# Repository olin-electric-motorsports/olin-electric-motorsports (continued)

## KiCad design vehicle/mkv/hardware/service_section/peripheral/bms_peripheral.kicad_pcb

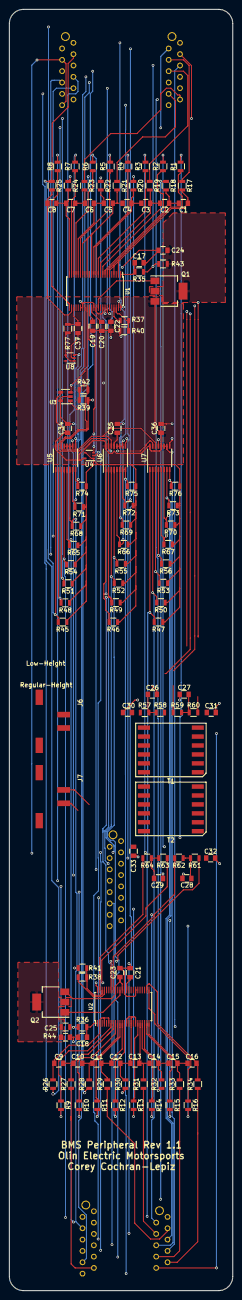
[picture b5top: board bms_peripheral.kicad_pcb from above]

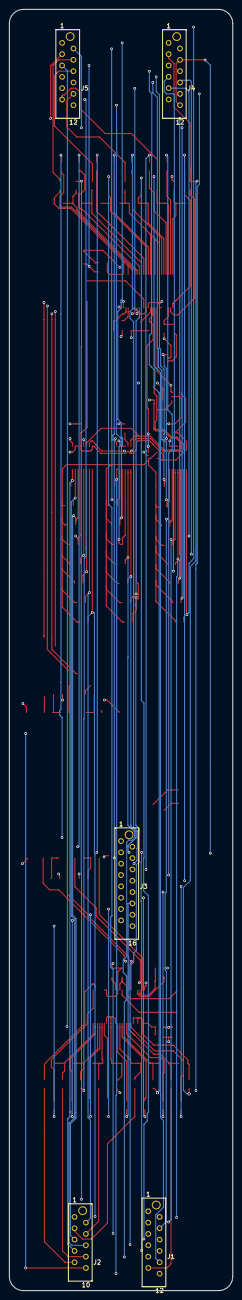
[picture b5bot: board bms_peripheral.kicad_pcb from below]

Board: 4 copper layers, 50.0 x 287.0 mm, 133 parts (5 on the bottom side), 138 nets.

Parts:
C1, C2, C3, C4, C5, C6, C7, C8, C9, C10, C11, C12, C13, C14, C15, C16, C26, C27, C28, C29, C30, C31, C32, C33, C37: C_10nF; C_0805_OEM
C17, C18, C24, C25: C_0.1uF; C_0805_OEM
C19, C20, C21, C22, C23: 1uF; C_0805_OEM
C34, C35, C36: C_1uF; C_0805_OEM
J1, J4: MM_F_VT_12; micromatch_female_vt_12
J2: MM_F_VT_10; micromatch_female_vert_10
J3: MM_F_VT_16; micromatch_female_vert_16
J5: MM_M_VT_12; micromatch_female_vt_12
J6, J7: MicroFit_RA_V_2_SMD; MicroFit_RA_2_SMD
Q1, Q2: NSS1C201MZ4; SOT-223
R1, R2, R3, R4, R5, R6, R7, R8, R9, R10, R11, R12, R13, R14, R15, R16, R39, R42: R_4.99K; R_0805_OEM
R17, R18, R19, R20, R21, R22, R23, R24, R25, R26, R27, R28, R29, R30, R31, R32, R33, R34, R35, R36, R43, R44, R77: R_100; R_0805_OEM
R37, R38, R40, R41: R_1K; R_0805_OEM
R45, R46, R47, R48, R49, R50, R51, R52, R53, R54, R55, R56, R65, R66, R67, R68, R69, R70, R71, R72, R73, R74, R75, R76: R_100K; R_0805_OEM
R57, R58, R59, R60, R61, R62, R63, R64: R_60.4; R_0805_OEM
T1, T2: T_LAN_SM91501ALE
U1, U2: LTC6811-1; TSSOP-48_LTC6811-1
U3: 24AA01; SOT-23-5_OEM_24AA01
U4, U8: MCP6001T-I-LT; SOT-353_SC-70-5
U5, U6, U7: LTC1380IGN; SSOP-16_3.9x4.9mm_P0.635mm

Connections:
/C0: J2.9, R34.1
/C1: J2.8, R33.1
/C1_T1: J2.7, R76.2, U7.8
/C1_T2: J2.6, R73.2, U7.7
/C1_T3: J2.5, R70.2, U7.6
/C2: J4.11, R32.1
/C3: J2.4, R31.1
/C3_T1: J4.9, R67.2, U7.5
/C3_T2: J4.8, R56.2, U7.4
/C3_T3: J4.7, R53.2, U7.3
/C4: J4.10, R30.1
/C5: J2.3, R29.1
/C5_T1: J2.2, R50.2, U7.2
/C5_T2: J2.1, R47.2, U7.1
/C5_T3: J1.12, R75.2, U6.8
/C6: J4.6, R28.1
/C7: J1.11, R27.1
/C7_T1: J4.2, R72.2, U6.7
/C7_T2: J4.1, R69.2, U6.6
/C7_T3: J5.12, R66.2, U6.5
/C8: J4.3, R25.1, R26.1
/C9: J1.10, R24.1
/C9_T1: J1.9, R55.2, U6.4
/C9_T2: J1.8, R52.2, U6.3
/C9_T3: J1.7, R49.2, U6.2
/C10: J5.11, R23.1
/C11: J1.6, R22.1
/C11_T1: J5.9, R46.2, U6.1
/C11_T2: J5.8, R74.2, U5.8
/C11_T3: J5.7, R71.2, U5.7
/C12: J5.10, R21.1
/C13: J1.5, R20.1
/C13_T1: J1.4, R68.2, U5.6
/C13_T2: J1.3, R65.2, U5.5
/C13_T3: J1.2, R54.2, U5.4
/C14: J5.6, R19.1
/C15: J1.1, R18.1
/C15_T1: J5.3, R51.2, U5.3
/C15_T2: J5.2, R48.2, U5.2
/C15_T3: J5.1, R45.2, U5.1
/C16: J5.4, R17.1
/GND1: C18.2, C21.2, C23.2, C25.2, C28.2, C29.2, C32.2, C33.2, J4.4, J4.12, R41.2, U2.30, U2.31, U2.36
/GND2: C17.2, C19.2, C20.2, C22.2, C24.2, C26.2, C27.2, C30.2, C31.2, C34.2, C35.2, C36.2, C37.2, J2.10, R40.2, U1.30, U1.31, U1.36, U3.2, U3.5, U4.2, U5.10, U5.11, U5.12, U5.13, U6.10, U6.11, U6.12, U7.10, U7.11, U7.13, U8.2
/IMA1: R62.2, T2.3, U2.41
/IMA2: R58.2, T1.3, U1.41
/IMB1: R64.2, T2.6, U2.47
/IMB2: R60.2, T1.6, U1.47
/IPA1: R61.1, T2.1, U2.42
/IPA2: R57.1, T1.1, U1.42
/IPB1: R63.1, T2.4, U2.48
/IPB2: R59.1, T1.4, U1.48
/Q1: J3.16, R16.2
/Q2: J3.15, R15.2
/Q3: J3.14, R14.2
/Q4: J3.13, R13.2
/Q5: J3.12, R12.2
/Q6: J3.11, R11.2
/Q7: J3.10, R10.2
/Q8: J3.9, R9.2
/Q9: J3.8, R8.2
/Q10: J3.7, R7.2
/Q11: J3.6, R6.2
/Q12: J3.5, R5.2
/Q13: J3.4, R4.2
/Q14: J3.3, R3.2
/Q15: J3.2, R2.2
/Q16: J3.1, R1.2
/SCL: R42.2, U1.33, U3.1, U5.15, U6.15, U7.15
/SDA: R39.2, U1.32, U3.3, U5.14, U6.14, U7.14
/TEMP_SENSE: C37.1, R77.1, U1.27
/V+1: J5.5, R36.1, R44.1
/V+2: J4.5, R35.1, R43.1
/VREF2: R45.1, R46.1, R47.1, R48.1, R49.1, R50.1, R51.1, R52.1, R53.1, R54.1, R55.1, R56.1, R65.1, R66.1, R67.1, R68.1, R69.1, R70.1, R71.1, R72.1, R73.1, R74.1, R75.1, R76.1, U4.1, U4.4
/VREG: C22.1, C34.1, C35.1, C36.1, Q1.3, R39.1, R42.1, U1.37, U1.40, U3.4, U4.5, U5.16, U6.13, U6.16, U7.12, U7.16, U8.5
/~DIS1: R16.1, U2.25
/~DIS2: R15.1, U2.23
/~DIS3: R14.1, U2.21
/~DIS4: R13.1, U2.19
/~DIS6: R12.1, U2.13
/~DIS7: R11.1, U2.11
/~DIS8: R10.1, U2.9
/~DIS9: R9.1, U2.7
unnamed: C1.1, R17.2, U1.2, U1.4, U1.6
unnamed: C1.2, C2.1, R18.2, U1.8
unnamed: C2.2, C3.1, R19.2, U1.10
unnamed: C3.2, C4.1, R20.2, U1.12
unnamed: C4.2, C5.1, R21.2, U1.14, U1.16, U1.18
unnamed: C5.2, C6.1, R22.2, U1.20
unnamed: C6.2, C7.1, R23.2, U1.22
unnamed: C7.2, C8.1, R24.2, U1.24
unnamed: C8.2, R25.2, U1.26
unnamed: C9.1, R26.2, U2.2, U2.4, U2.6
unnamed: C9.2, C10.1, R27.2, U2.8
unnamed: C10.2, C11.1, R28.2, U2.10
unnamed: C11.2, C12.1, R29.2, U2.12
unnamed: C12.2, C13.1, R30.2, U2.14, U2.16, U2.18
unnamed: C13.2, C14.1, R31.2, U2.20
unnamed: C14.2, C15.1, R32.2, U2.22
unnamed: C15.2, C16.1, R33.2, U2.24
unnamed: C16.2, R34.2, U2.26
unnamed: C17.1, R35.2, U1.1
unnamed: C18.1, R36.2, U2.1
unnamed: C19.1, U1.34, U4.3
unnamed: C20.1, U1.35
unnamed: C21.1, U2.35
unnamed: C23.1, Q2.3, U2.37, U2.40
unnamed: C24.1, Q1.2, Q1.4, R43.2
unnamed: C25.1, Q2.2, Q2.4, R44.2
unnamed: C26.1, R57.2, R58.1
unnamed: C27.1, R59.2, R60.1
unnamed: C28.1, R61.2, R62.1
unnamed: C29.1, R63.2, R64.1
unnamed: C30.1, T1.2
unnamed: C31.1, T1.5
unnamed: C32.1, T2.2
unnamed: C33.1, T2.5
unnamed: J6.1, T1.12
unnamed: J6.2, T1.10
unnamed: J7.1, T2.9
unnamed: J7.2, T2.7
unnamed: Q1.1, U1.38
unnamed: Q2.1, U2.38
unnamed: R1.1, U1.7
unnamed: R2.1, U1.9
unnamed: R3.1, U1.11
unnamed: R4.1, U1.13
unnamed: R5.1, U1.19
unnamed: R6.1, U1.21
unnamed: R7.1, U1.23
unnamed: R8.1, U1.25
unnamed: R37.1, R40.1, U1.46
unnamed: R37.2, U1.45
unnamed: R38.1, R41.1, U2.46
unnamed: R38.2, U2.45
unnamed: R77.2, U8.1, U8.4
unnamed: T1.7, T2.10
unnamed: T1.9, T2.12
unnamed: U5.9, U6.9, U7.9, U8.3

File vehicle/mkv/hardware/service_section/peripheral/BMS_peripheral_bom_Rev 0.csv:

Component,Description,Part,References,Value,Footprint,Quantity Per PCB,Datasheet,MPN,MFN,PurchasingLink
1,"Capacitor, 1uF, 25V, 10%, 0805",C_1uF,C19 C20 C21 C22 C23,1uF,C_0805_OEM,5,http://www.samsungsem.com/kr/support/product-search/mlcc/__i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,1276-2887-1-ND,DK,https://www.digikey.com/product-detail/en/samsung-electro-me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
2,"Capacitor, 0.1uF, 50V, 5%, 0805",C_0.1uF,C17 C18 C24 C25,C_0.1uF,C_0805_OEM,4,http://datasheets.avx.com/X7RDielectric.pdf,478-3352-1-ND,DK,https://www.digikey.com/products/en?keywords=478-3352-1-ND
3,"Capacitor, 10nF 50V X7R 0805",C_10nF,C1 C2 C3 C4 C5 C6 C7 C8 C9 C10 C11 C12 C13 C14 C15 C16 C26 C27 C28 C29 C30 C31 C32 C33 C37,C_10nF,C_0805_OEM,25,http://www.samsungsem.com/kr/support/product-search/mlcc/__i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,1276-1015-1-ND,DK,https://www.digikey.com/product-detail/en/samsung-electro-me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
4,"Capacitor, 1uF, 25V, 10%, 0805",C_1uF,C34 C35 C36,C_1uF,C_0805_OEM,3,http://www.samsungsem.com/kr/support/product-search/mlcc/__i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,1276-2887-1-ND,DK,https://www.digikey.com/product-detail/en/samsung-electro-me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
5,Micro-MaTch connector 10 pin female vertical,MM_F_VT_10,J2,MM_F_VT_10,micromatch_female_vert_10,1,http://www.te.com/commerce/DocumentDelivery/DDEController?Ac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,1-338068-0,TE,http://www.te.com/global-en/product-1-338068-0.html
6,Micro-MaTch connector 12 pin female vertical,MM_F_VT_12,J1 J4,MM_F_VT_12,micromatch_female_vt_12,2,http://www.te.com/commerce/DocumentDelivery/DDEController?Ac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,1-338068-2,TE,http://www.te.com/global-en/product-1-338068-2.html
7,Micro-MaTch connector 16 pin female vertical,MM_F_VT_16,J3,MM_F_VT_16,micromatch_female_vert_16,1,http://www.te.com/commerce/DocumentDelivery/DDEController?Ac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,1-338068-6,TE,http://www.te.com/global-en/product-1-338068-6.html
8,Micro-MaTch connector 12 pin male vertical,MM_M_VT_12,J5,MM_M_VT_12,micromatch_female_vt_12,1,http://www.te.com/commerce/DocumentDelivery/DDEController?Ac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,1-215464-2,TE,http://www.te.com/global-en/product-1-215464-2.html
9,"100V, 2.0A, Low VCE NPN Transistor",NSS1C201MZ4,Q1 Q2,NSS1C201MZ4,SOT-223,2,http://www.onsemi.com/pub/Collateral/NSS1C201MZ4-D.PDF,NSS1C201MZ4T3GOSCT-ND,DK,https://www.digikey.com/product-detail/en/on-semiconductor/N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
10,"Resistor, 100, 0.25W, 1%, 0805",R_100,R17 R18 R19 R20 R21 R22 R23 R24 R25 R26 R27 R28 R29 R30 R31 R32 R33 R34 R35 R36 R43 R44 R77,R_100,R_0805_OEM,23,https://www.seielect.com/Catalog/SEI-rncp.pdf,RNCP0805FTD100RCT-ND,DK,https://www.digikey.com/products/en?keywords=RNCP0805FTD100RCT-ND
11,"Resistor, 100K, 0.125W, 1%, 0805",R_100K,R45 R46 R47 R48 R49 R50 R51 R52 R53 R54 R55 R56 R65 R66 R67 R68 R69 R70 R71 R72 R73 R74 R75 R76,R_100K,R_0805_OEM,24,https://industrial.panasonic.com/cdbs/www-data/pdf/RDA0000/A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,P100KCCT-ND,DK,https://www.digikey.com/product-detail/en/panasonic-electron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
12,"Resistor, 1K, 0.25W, 1%, 0805",R_1K,R37 R38 R40 R41,R_1K,R_0805_OEM,4,https://www.seielect.com/Catalog/SEI-rncp.pdf,RNCP0805FTD1K00CT-ND,DK,https://www.digikey.com/products/en?keywords=RNCP0805FTD1K00CT-ND
13,4.99k resistor,R_4.99K,R1 R2 R3 R4 R5 R6 R7 R8 R9 R10 R11 R12 R13 R14 R15 R16 R39 R42,R_4.99K,R_0805_OEM,18,https://www.digikey.com/product-detail/en/yageo/RC0402FR-074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,RNCP0805FTD4K99CT-ND,DK,https://www.digikey.com/product-detail/en/stackpole-electron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
14,"Resistor, 60.4, 0.1%, 0.125W, 0805",R_60.4,R57 R58 R59 R60 R61 R62 R63 R64,R_60.4,R_0805_OEM,8,https://industrial.panasonic.com/cdbs/www-data/pdf/RDM0000/A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,P60.4DACT-ND,DK,https://www.digikey.com/product-detail/en/panasonic-electron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
15,Transformer LAN 10/100 base-T,T_LAN_7490100111A,T1 T2,T_LAN_7490100111A,T_LAN_7490100111A,2,https://katalog.we-online.de/pbs/datasheet/7490100111A.pdf,732-5711-1-ND,DK,https://www.digikey.com/product-detail/en/wurth-electronics-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
16,IC EEPROM 1K I2C 400KHZ 8DIP,24AA01,U3,24AA01,SOT-23-5_OEM_24AA01,1,http://ww1.microchip.com/downloads/en/DeviceDoc/21711J.pdf,CAT24AA01TDI-GT3OSCT-ND,DK,https://www.digikey.com/product-detail/en/on-semiconductor/C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
17,Single-Ended 8-Channel/ Differential 4-Channel Analog Multiplexer with SMBus Interface,LTC1380IGN,U5 U6 U7,LTC1380IGN,SSOP-16_3.9x4.9mm_P0.635mm,3,https://www.analog.com/media/en/technical-documentation/data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,LTC1380IGN#PBF-ND,DK,https://www.digikey.com/product-detail/en/linear-technology-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
18,LTC6811-1,LTC6811-1,U1 U2,LTC6811-1,TSSOP-48_LTC6811-1,2,https://www.analog.com/media/en/technical-documentation/data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,LTC6811IG-1-PBF-ND,DK,https://www.digikey.com/product-detail/en/linear-technology-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
19,"Single op-amp, general purpose, -40-+85 C, SC-70-5",MCP6001T-I-LT,U4 U8,MCP6001T-I-LT,SOT-353_SC-70-5,2,http://ww1.microchip.com/downloads/en/DeviceDoc/21733j.pdf,MCP6001T-I/LTCT-ND,DK,https://www.digikey.com/product-detail/en/microchip-technolo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
,,,,,,,,,,
,,,,,,,,,,
,,,,,,,,,,
,,,,,,,,,,
,,,,,,,,,,
Component Groups:,19,,,,,,,,,
Component Count:,131,,,,,,,,,
Fitted Components:,131,,,,,,,,,
Number of PCBs:,1,,,,,,,,,
Total components:,131,,,,,,,,,
Schematic Version:,Rev 0,,,,,,,,,
Schematic Date:,2019-09-17,,,,,,,,,
PCB Variant:,default,,,,,,,,,
BoM Date:,Mon 11 Nov 2019 08:39:12 PM EST,,,,,,,,,
Schematic Source:,/home/vscheyer/Desktop/Formula/MKV-Boards/Boards/BMS_Peripheral/BMS_peripheral.sch,,,,,,,,,
KiCad Version:,Eeschema 5.0.2-bee76a0~70~ubuntu16.04.1,,,,,,,,,

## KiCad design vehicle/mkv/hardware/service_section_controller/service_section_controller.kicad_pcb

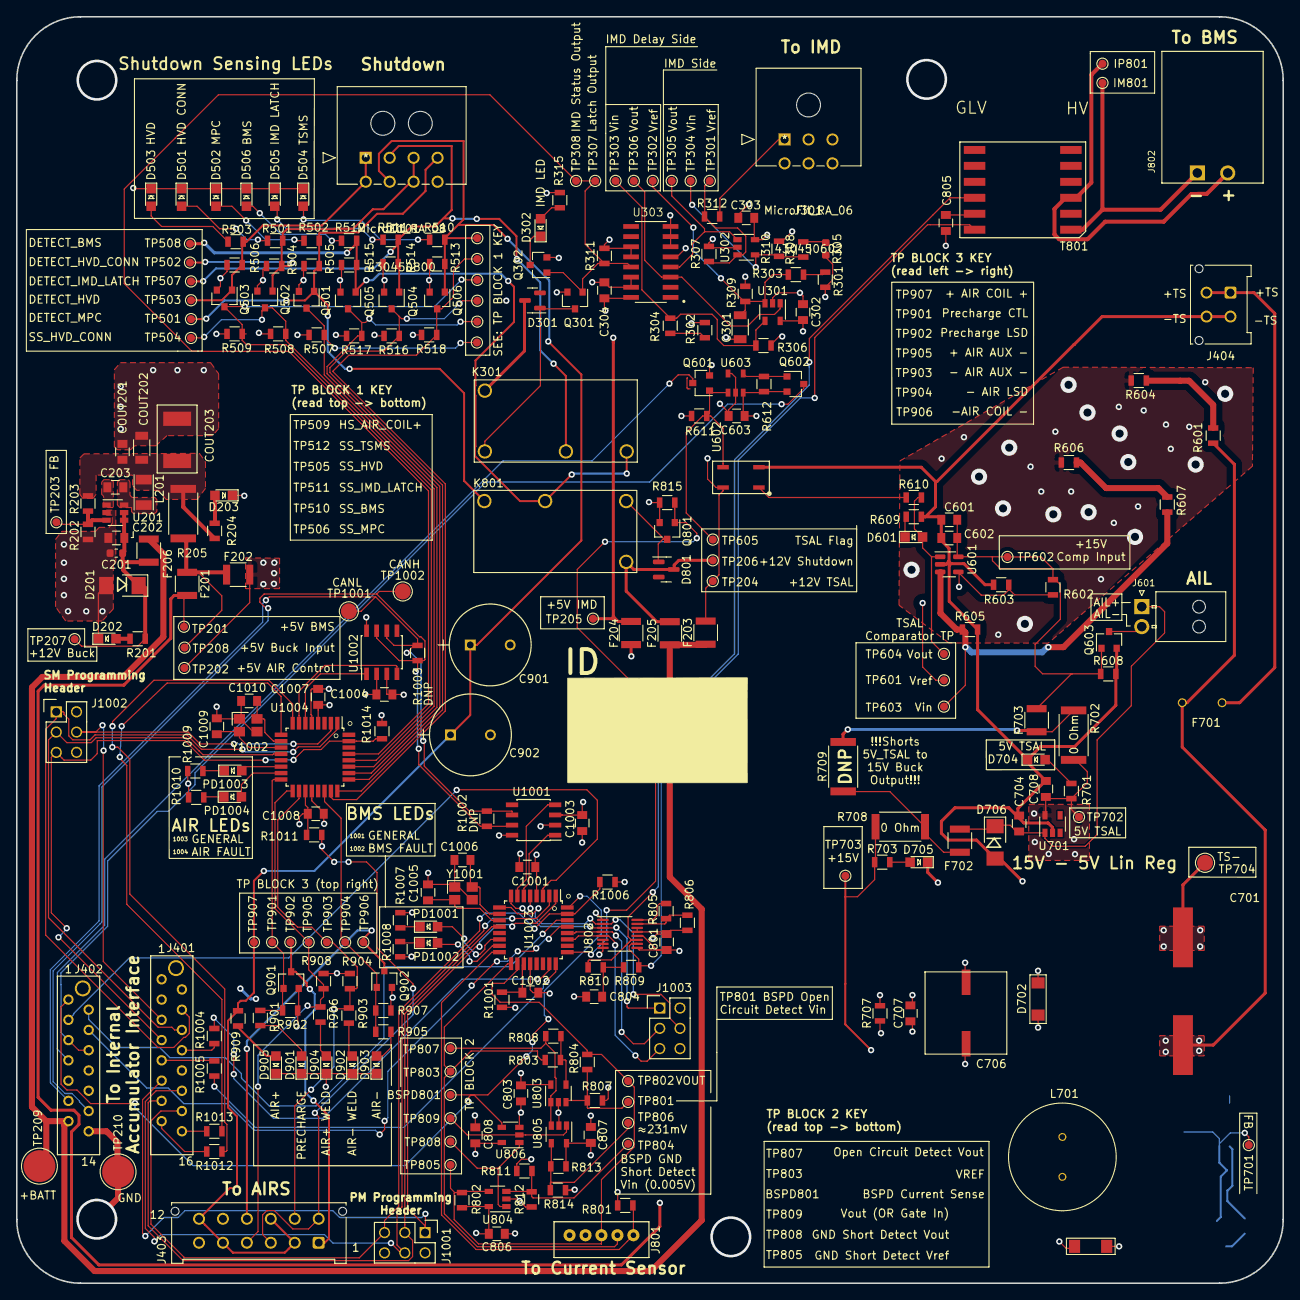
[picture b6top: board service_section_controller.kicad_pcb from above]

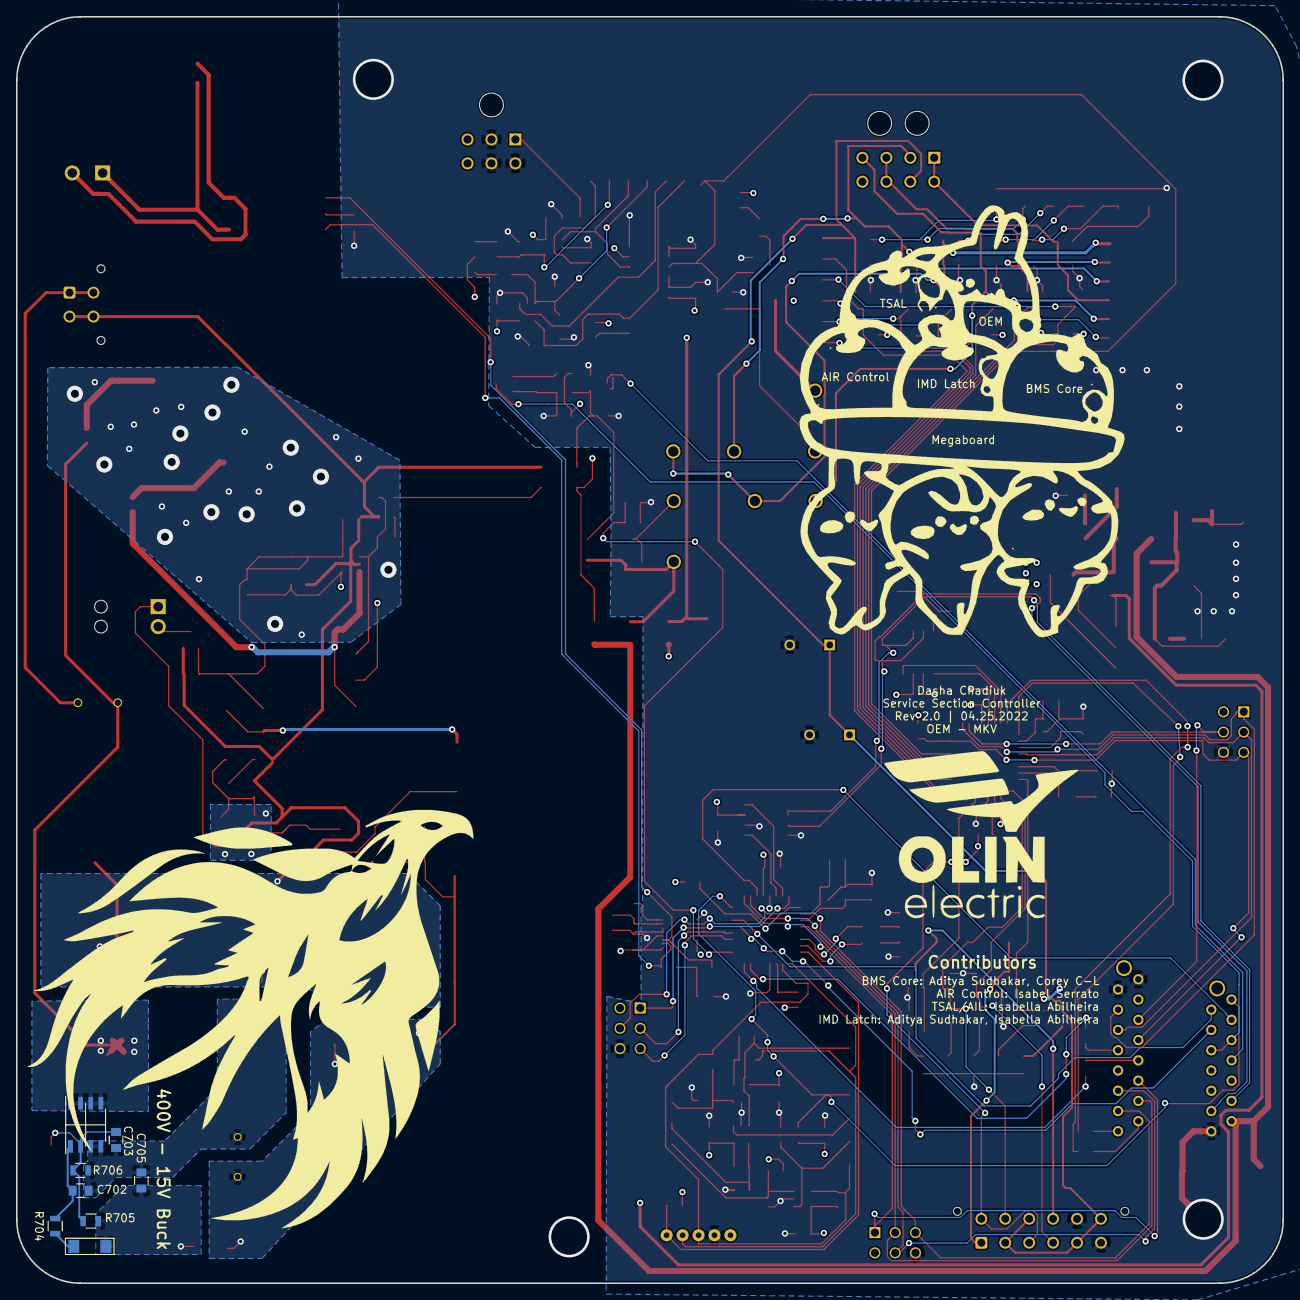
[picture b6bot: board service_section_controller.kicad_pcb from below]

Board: 4 copper layers, 158.8 x 158.8 mm, 283 parts (8 on the bottom side), 151 nets.

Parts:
BSPD801: Test_Point_SMD; TestPoint_Pad_D1.0mm
C201: C_2.2uF; C_0603_1608Metric
C202, C203, C302, C303, C304, C602, C801, C803, C806, C807, C808, C1001, C1003, C1004, C1007: C_0.1uF; C_0805_OEM
C301: C_22uF; C_1206_OEM
C601: C_10uF; C_0805_OEM
C603, C704, C707, C708: C_1uF; C_0805_OEM
C701: C_10uF_450V
C702: C_2.2uF; C_0805_OEM
C703: C_470pF; C_0805_OEM
C705: C_.22uF; C_0805_OEM
C706: C_100uF+
C804, C805: C_10nF; C_0805_OEM
C901, C902: CP_1mF; C_Radial_D10_L13_P5_OEM
C1002, C1008: C_100pF; C_0805_OEM
C1005, C1006, C1009, C1010: C_30pF; C_0805_OEM
COUT201: C_47uF; C_0805_OEM
COUT202: C_22uF; C_1206_OEM
COUT203: C_33uF; Fuse_1812
D201, D706: D_Zener_18V; DO-214AA
D202, D203, D302, D501, D502, D503, D504, D505, D506, D601, D704, D705, D901, D902, D903, D904, D905: LED_0805; LED_0805_OEM
D301, D801: BAS40-00; SOT-23
D701, D702, D703: Diode_600V_1A_SM
F201, F202, F203, F204, F205, F206, F702, F703: 500mA; Fuse_1210
F701: F_21mA_420V
IM801: Test_Point_SMD; TestPoint_Pad_D1.0mm
IP801: Test_Point_SMD; TestPoint_Pad_D1.0mm
J301: MicroFit_RA_06; 430450602
J401: MM_F_VT_16; micromatch_female_vert_16
J402: MM_F_VT_14; micromatch_female_vert_14
J403: MicroFit_VT_12
J404: MicroFit_VT_4
J601: NanoFit_2; NanoFit_Molex_1x02x2.50mm_Angled_OEM
J801: B5B-PH-K-S
J802: isoSPI-Cutout; iso_spi_cutout
J1001, J1002, J1003: CONN_02X03; Pin_Header_Straight_2x03
J1101: MicroFit_RA_08; 430450800
K301, K801: G5Q-1A4-DC12; Relay_SPST_OMRON-G5Q-1A4_OEM
L201: L_100uH; L_100uH_OEM
L701: L_1.2mH
PD1001, PD1002, PD1003, PD1004: LED_0805; LED_0805_OEM
Q301, Q302, Q501, Q502, Q503, Q504, Q505, Q506, Q601, Q602, Q603, Q801, Q901, Q902: SSM3K333R; SOT-23F
R201, R301, R307, R315, R501, R502, R503, R510, R511, R512, R602, R609, R703, R805, R806, R812, R909: R_1K; R_0805_OEM
R202: R_25K; R_0805_OEM
R203, R310, R504, R505, R506, R513, R514, R515: R_100K; R_0805_OEM
R204, R701, R901, R903, R905, R906, R1004, R1005, R1007, R1008, R1009, R1010, R1012, R1013: R_200; R_0805_OEM
R205, R702, R708, R709: R_0_2512; R_2512_OEM
R302: R_2.2K; R_0805_OEM
R303: R_120K; R_0805_OEM
R304: R_300K; R_0805_OEM
R305: R_0; R_0603_1608Metric
R306, R311: R_604K; R_0805_OEM
R308: R_200K; R_0805_OEM
R309: R_1.82M; R_0805_OEM
R312, R707: R_3K; R_0805_OEM
R507, R508, R509, R516, R517, R518, R605, R608, R611, R612, R704, R801, R802, R803, R804, R807, R808, R814, R815, R902, R904, R907, R908, R1006, R1014: R_10K; R_0805_OEM
R601, R604, R606, R607: R_270K; R_0805_OEM
R603: R_120; R_0805_OEM
R610: R_499; R_0805_OEM
R705: R_23.7K; R_0805_OEM
R706: R_4.99K; R_0805_OEM
R809, R810: R_60.4; R_0805_OEM
R811: R_1M; R_0805_OEM
R813: R_475; R_0805_OEM
R1001, R1011: R_100; R_0805_OEM
R1002, R1003: R_120_DNP; R_0805_OEM
T801: T_LAN_SM91501ALE
TP201: 5V_BMS; TestPoint_Pad_D1.0mm
TP202: 5V_AIR_CONTROL; TestPoint_Pad_D1.0mm
TP203, TP701: FB; TestPoint_Pad_D1.0mm
TP204: 12V_TSAL; TestPoint_Pad_D1.0mm
TP205: 5V_IMD; TestPoint_Pad_D1.0mm
TP206: 12V_SHUTDOWN; TestPoint_Pad_D1.0mm
TP207: 12V_BUCK; TestPoint_Pad_D1.0mm
TP208: BUCK_OUTPUT; TestPoint_Pad_D1.0mm
TP209: +Batt; TestPoint_Pad_D4.0mm
TP210: LV_GND; TestPoint_Pad_D4.0mm
TP301: IMD_OUTPUT; TestPoint_Pad_D1.0mm
TP302, TP303, TP306, TP801, TP804, TP805, TP806, TP807, TP808, TP809: Test_Point_SMD; TestPoint_Pad_D1.0mm
TP304: 1.6V_OPAMP; TestPoint_Pad_D1.0mm
TP305: OPAMP_OUTPUT; TestPoint_Pad_D1.0mm
TP307: LATCH_OUTPUT; TestPoint_Pad_D1.0mm
TP308: IMD_STATUS_OUTPUT; TestPoint_Pad_D1.0mm
TP501: DETECT_MPC; TestPoint_Pad_D1.0mm
TP502: DETECT_HVD_CONN; TestPoint_Pad_D1.0mm
TP503: DETECT_HVD; TestPoint_Pad_D1.0mm
TP504: SS_HVD_CONN; TestPoint_Pad_D1.0mm
TP505: SS_HVD; TestPoint_Pad_D1.0mm
TP506: SS_MPC; TestPoint_Pad_D1.0mm
TP507: DETECT_IMD_LATCH; TestPoint_Pad_D1.0mm
TP508: DETECT_BMS; TestPoint_Pad_D1.0mm
TP509: DETECT_TSMS; TestPoint_Pad_D1.0mm
TP510: SS_BMS; TestPoint_Pad_D1.0mm
TP511: SS_IMD_LATCH; TestPoint_Pad_D1.0mm
TP512: SS_TSMS; TestPoint_Pad_D1.0mm
TP601, TP803: VREF; TestPoint_Pad_D1.0mm
TP602: 5V+; TestPoint_Pad_D1.0mm
TP603: VIN; TestPoint_Pad_D1.0mm
TP604: COMPARATOR_OUTPUT; TestPoint_Pad_D1.0mm
TP605: TSAL_FLAG; TestPoint_Pad_D1.0mm
TP702: 5V_TSAL; TestPoint_Pad_D1.0mm
TP703: 15V+_OUTPUT; TestPoint_Pad_D1.0mm
TP704: TS-; TestPoint_Pad_D2.0mm
TP802: VOUT; TestPoint_Pad_D1.0mm
TP901: PRECHARGE_CTL; TestPoint_Pad_D1.0mm
TP902: PRECHARGE_LSD; TestPoint_Pad_D1.0mm
TP903: -AIR_WELD_DETECT; TestPoint_Pad_D1.0mm
TP904: -AIR_LSD; TestPoint_Pad_D1.0mm
TP905: +AIR_WELD_DETECT; TestPoint_Pad_D1.0mm
TP906: -AIR_COIL-; TestPoint_Pad_D1.0mm
TP907: +AIR_COIL+; TestPoint_Pad_D1.0mm
TP1001: CAN_L; TestPoint_Pad_D2.0mm
TP1002: CANH; TestPoint_Pad_D2.0mm
U201: TPS560430YF; SOT-23-6_OEM
U301, U302: TLV3701QDBVRG4Q1; SOT-23-5_OEM
U303: CD4044BDR; SOIC127P600X175-16N
U601: MCP6001; SOT-23-5
U602: CPC1025NTR; 4-pin_SOP
U603: BU4S11G2-TR; SSOP5
U701: AP7370; SOT-23-5
U702: MP9488; Converter_DCDC_MPS_MP9488
U802: LTC6820HMS; MSOP-16_3x4mm_P0.5mm
U803, U804, U805: MCP6001; SOT-23-5_OEM
U806: SN74LVC1G32DBVR; SOT-23-5_OEM
U1001, U1002: MCP2561-E_SN; SOIC-8_3.9x4.9mm_Pitch1.27mm_OEM
U1003: ATMEGA64M1; TQFP-32_7x7mm_Pitch0.8mm
U1004: ATMEGA16M1; TQFP-32_7x7mm_Pitch0.8mm
Y1001, Y1002: Crystal_SMD; Crystal_SMD_FA238

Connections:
+5V: F201.1, F202.1, R205.1, TP208.1
+5V_AIR_CONTROL: C1004.1, C1007.1, F202.2, F204.1, J401.10, J403.3, J403.7, J1002.2, R507.1, R508.1, R509.1, R516.1, R517.1, R518.1, R1011.1, R1014.1, TP202.1, U1002.3, U1004.4
+5V_BMS: C801.1, C803.1, C806.1, C807.1, C808.1, C1001.1, C1003.1, F201.2, J401.3, J801.1, J1001.2, J1003.2, R801.1, R802.2, R811.1, R813.2, R1001.1, R1006.1, TP201.1, U802.6, U802.7, U802.8, U802.9, U802.12, U803.5, U804.5, U805.5, U806.5, U1001.3, U1003.4
+5V_IMD: C302.2, C303.2, C304.2, F204.2, R301.2, R302.2, R305.2, R315.1, TP205.1, U301.5, U302.5, U303.5, U303.16
+5V_TSAL: F703.1, R702.2, R709.2
+5V__TSAL_FUSED: C601.2, C602.2, F703.2, Q603.1, R602.2, R608.1, TP602.1, U601.5
+12V_SHUTDOWN: D301.3, D801.3, F205.2, J301.3, K301.5, K801.5, TP206.1
+12V_TSAL: C603.2, F203.2, J402.8, J402.9, J402.10, TP204.1, U602.4, U603.2, U603.5
+15V: F702.1, R708.1, R709.1
+15V_FUSED: C704.1, D706.1, F702.2, J601.1, U701.1
+AIR_AUX-: J403.4, R906.1, R908.1, TP905.1, U1004.17
+AIR_COIL+: C901.1, C902.1, J403.2, J403.5, J403.9, J403.12, J1101.6, Q506.1, R510.1, R513.1, R909.1, TP509.1, TP907.1
+AIR_COIL-: C201.2, C202.2, C301.2, C302.1, C303.1, C304.1, C603.1, C801.2, C803.2, C804.2, C805.2, C806.2, C807.2, C808.2, C901.2, C902.2, C1001.2, C1002.2, C1003.2, C1004.2, C1005.2, C1006.2, C1007.2, C1008.2, C1009.2, C1010.2, COUT201.2, COUT202.2, COUT203.2, D201.2, D202.1, D203.1, D501.1, D502.1, D503.1, D504.1, D505.1, D506.1, D901.1, D902.1, D903.1, D904.1, D905.1, J301.2, J301.4, J301.5, J401.1, J401.2, J402.14, J403.6, J403.11, J801.2, J1001.6, J1002.6, J1003.6, Q301.2, Q302.2, Q501.2, Q502.2, Q503.2, Q504.2, Q505.2, Q506.2, Q601.2, Q602.2, Q801.2, Q901.2, Q902.2, R202.2, R306.1, R307.2, R309.2, R310.2, R311.2, R504.2, R505.2, R506.2, R513.2, R514.2, R515.2, R611.2, R612.2, R806.2, R807.1, R812.2, R814.1, R815.1, R902.2, R904.2, R907.2, R908.2, R1007.2, R1008.2, R1009.2, R1010.2, TP210.1, U201.2, U301.2, U302.2, U303.6, U303.7, U303.8, U303.11, U303.12, U303.14, U303.15, U603.3, U802.1, U802.13, U802.14, U803.2, U804.2, U805.2, U806.3, U1001.2, U1001.8, U1002.2, U1002.8, U1003.5, U1003.20, U1004.5, U1004.20, Y1001.2, Y1001.4, Y1002.2, Y1002.4
+BATT: F203.1, F205.1, F206.1, J402.13, TP209.1
+TS: F701.2, J404.1, J404.3
-AIR_AUX-: J403.8, R903.1, R904.1, TP903.1, U1004.18
-AIR_COIL-: J403.10, Q902.3, TP906.1
-AIR_LSD: Q902.1, R905.1, R907.1, TP904.1, U1004.22
-TS: C601.1, C602.1, C701.1, C704.2, C706.2, C707.2, C708.2, D702.1, D704.1, D705.1, D706.2, J404.2, J404.4, Q603.2, R603.2, R605.2, R608.2, R609.2, R707.2, TP704.1, U601.2, U602.2, U701.2
/micros/PM_DBG_1: PD1001.2, U1003.14
/micros/PM_DBG_2: PD1002.2, U1003.15
/micros/PM_RXCAN: U1001.4, U1003.7
/micros/PM_TXCAN: U1001.1, U1003.6
/micros/SM_DBG_1: PD1003.2, U1004.14
/micros/SM_DBG_2: PD1004.2, U1004.15
/micros/SM_RXCAN: U1002.4, U1004.7
/micros/SM_TXCAN: U1002.1, U1004.6
/power_main/+12V_BUCK: C201.1, C202.1, D201.1, F206.2, R201.1, TP207.1, U201.4, U201.5
/power_secondary.sch/FB: C703.1, R705.2, R706.1, TP701.1, U702.2
/power_secondary.sch/SW: C702.2, C703.2, C705.2, D702.2, L701.1, R706.2, U702.3, U702.4
/power_secondary.sch/VCC: C702.1, R704.2, U702.1
/tsal_ail/TSAL_FLAG: Q601.1, R611.1, TP605.1, U602.3, U603.1
AIL-: J601.2, Q603.3
BMS_RELAY_DRIVE: Q801.1, R815.2, U1003.25
BSPD_CURRENT_SENSE: BSPD801.1, J402.1, U806.4, U1003.32
CANH: J402.12, R1002.1, R1003.1, TP1002.1, U1001.7, U1002.7
CANL: J402.11, R1002.2, R1003.2, TP1001.1, U1001.6, U1002.6
CHARGE_ENABLE1: J402.4, U1003.29
CHARGE_ENABLE2: J402.2, U1003.30
CS_ISO: J1003.5, U802.5, U1003.27
DETECT_BMS: K301.3, K801.2, Q505.1, R512.1, R515.1, TP508.1
DETECT_HVD: J1101.1, J1101.5, Q503.1, R503.1, R506.1, TP503.1
DETECT_HVD_CONN: J1101.3, J1101.7, Q502.1, R501.1, R504.1, TP502.1
DETECT_IMD_LATCH: J1101.2, K301.2, Q504.1, R511.1, R514.1, TP507.1
DETECT_MPC: J1101.4, K801.3, Q501.1, R502.1, R505.1, TP501.1
FAN_PWM: J402.3, U1003.3
IM: IM801.1, J802.1, T801.1
IMD_Output: J301.1, R312.2
IMD_STATUS_OUTPUT: Q301.1, Q302.1, R311.1, TP307.1, TP308.1, U303.13, U1004.29
IP: IP801.1, J802.2, T801.3
MISO_ISO: J1003.1, U802.3, U1003.8
MOSI_ISO: J1003.4, U802.2, U1003.9
unnamed: C203.1, L201.1, U201.6
unnamed: C203.2, U201.1
unnamed: C301.1, R303.1, R309.1, TP302.1, U301.3
unnamed: C705.1, D701.1, D703.2, R705.1
unnamed: C706.1, C707.1, D703.1, L701.2, R703.1, R707.1, R708.2, TP703.1
unnamed: C708.1, R701.1, R702.1, TP702.1, U701.5
unnamed: C804.1, R809.2, R810.1
unnamed: C805.1, T801.11
unnamed: C1002.1, R1001.2, U1003.19
unnamed: C1005.1, U1003.11, Y1001.1
unnamed: C1006.1, U1003.10, Y1001.3
unnamed: C1008.1, R1011.2, U1004.19
unnamed: C1009.1, U1004.11, Y1002.1
unnamed: C1010.1, U1004.10, Y1002.3
unnamed: COUT201.1, COUT202.1, COUT203.1, L201.2, R203.2, R204.1, R205.2
unnamed: D202.2, R201.2
unnamed: D203.2, R204.2
unnamed: D301.1, K301.1, Q301.3
unnamed: D302.1, Q302.3
unnamed: D302.2, R315.2
unnamed: D501.2, R501.2
unnamed: D502.2, R502.2
unnamed: D503.2, R503.2
unnamed: D504.2, R510.2
unnamed: D505.2, R511.2
unnamed: D506.2, R512.2
unnamed: D601.1, R609.1
unnamed: D601.2, R610.2, TP604.1, U601.1
unnamed: D701.2, R704.1
unnamed: D704.2, R701.2
unnamed: D705.2, R703.2
unnamed: D801.1, K801.1, Q801.3
unnamed: D901.2, R901.2
unnamed: D902.2, R903.2
unnamed: D903.2, R905.2
unnamed: D904.2, R906.2
unnamed: D905.2, R909.2
unnamed: PD1001.1, R1007.1
unnamed: PD1002.1, R1008.1
unnamed: PD1003.1, R1009.1
unnamed: PD1004.1, R1010.1
unnamed: Q602.1, R612.1, U603.4
unnamed: R202.1, R203.1, TP203.1, U201.3
unnamed: R301.1, R303.2
unnamed: R302.1, R304.2
unnamed: R304.1, R306.2, TP303.1, U301.4
unnamed: R305.1, R308.2
unnamed: R307.1, R312.1, TP301.1, U302.3
unnamed: R308.1, R310.1, TP304.1, U302.4
unnamed: R601.1, R604.2
unnamed: R602.1, R603.1, TP601.1, U601.4
unnamed: R604.1, R606.2
unnamed: R605.1, R607.1, TP603.1, U601.3
unnamed: R606.1, R607.2
unnamed: R610.1, U602.1
unnamed: R803.2, R808.1, U803.4
unnamed: R804.2, R807.2, TP801.1, U803.3
unnamed: R805.1, U802.16
unnamed: R805.2, R806.1, U802.15
unnamed: R808.2, TP807.1, U803.1, U805.3
unnamed: R809.1, T801.12, U802.10
unnamed: R810.2, T801.10, U802.11
unnamed: R811.2, R812.1, TP804.1, U804.3
unnamed: R813.1, R814.2, TP806.1, U805.4
unnamed: R1004.2, U1003.23
unnamed: R1005.2, U1003.24
unnamed: R1012.2, U1004.8
unnamed: R1013.2, U1004.9
unnamed: TP305.1, U302.1, U303.4
unnamed: TP306.1, U301.1, U303.3
unnamed: TP808.1, U804.1, U806.1
unnamed: TP809.1, U805.1, U806.2
PM_MISO: J401.11, J1001.1, U1003.1
PM_MOSI: J401.12, J1001.4, U1003.2
PM_RESET: J401.14, J1001.5, R1006.2, U1003.31
PM_RJ45_LEDG: J401.8, R1004.1
PM_RJ45_LEDO: J401.9, R1005.1
PM_SCK: J401.13, J1001.3, U1003.12
PRECHARGE_CTL: Q901.1, R901.1, R902.1, TP901.1, U1004.16
PRECHARGE_LSD: J403.1, Q901.3, TP902.1
SCK_ISO: J1003.3, U802.4, U1003.28
SM_MISO: J401.4, J1002.1, U1004.1
SM_MOSI: J401.5, J1002.4, U1004.2
SM_RESET: J401.7, J1002.5, R1014.2, U1004.31
SM_RJ45_LEDG: J401.15, R1012.1
SM_RJ45_LEDO: J401.16, R1013.1
SM_SCK: J401.6, J1002.3, U1004.12
SS_BMS: Q505.3, R517.2, TP510.1, U1004.25
SS_HVD: Q503.3, R509.2, TP505.1, U1004.28
SS_HVD_CONN: Q502.3, R508.2, TP504.1, U1004.27
SS_IMD_LATCH: Q504.3, R516.2, TP511.1, U1004.24
SS_MPC: Q501.3, R507.2, TP506.1, U1004.26
SS_TSMS: Q506.3, R518.2, TP512.1, U1004.23
TS+_FUSED: C701.2, F701.1, R601.2, U702.5, U702.6, U702.7, U702.8
TSAL_GREEN-: J402.5, J402.6, Q602.3
TSAL_RED-: J402.7, Q601.3
VOUT: J801.3, R802.1, R804.1, TP802.1, TP805.1, U804.4, U1003.18
VREF: J801.4, R803.1, TP803.1, U1003.17
nOCD: J801.5, R801.2, U1003.16

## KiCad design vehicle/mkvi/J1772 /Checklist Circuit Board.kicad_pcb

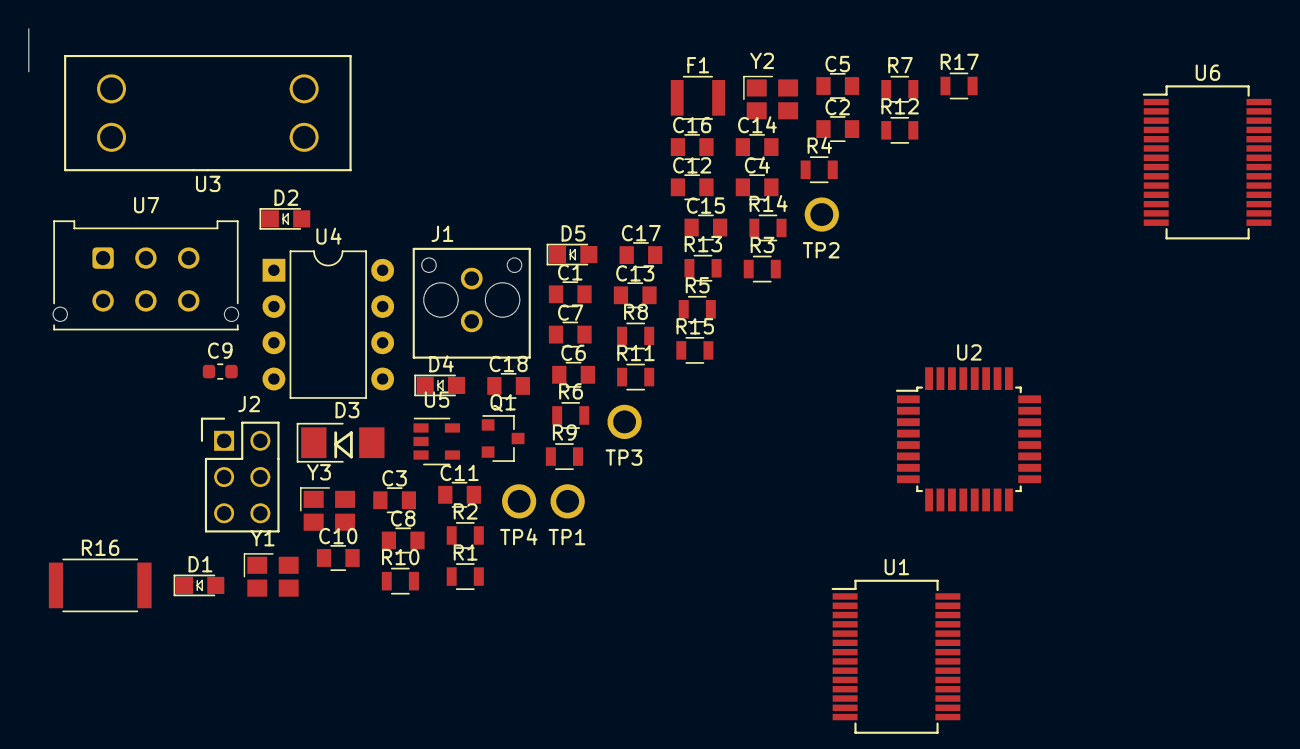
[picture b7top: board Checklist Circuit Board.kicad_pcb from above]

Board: 2 copper layers, 58 parts (0 on the bottom side), 46 nets, no tracks yet.

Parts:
C1, C2, C6, C7, C17, C18: C_30pF; C_0805_OEM
C3, C4, C5, C8, C10, C11, C14, C15, C16: C_0.1uF; C_0805_OEM
C9: C_100nF; C_0603_1608Metric
C12, C13: C_1uF; C_0805_OEM
D1: LED_0805_Red; LED_0805_OEM
D2, D4, D5: LED_0805; LED_0805_OEM
D3: D_Zener_18V; DO-214AA
F1: F_500mA_16V; Fuse_1210
J1: MicroFit_V_2
J2: CONN_02X03; Pin_Header_Straight_2x03
Q1: SSM3K333R; SOT-23F
R1, R2, R13, R15: R_100; R_0805_OEM
R3: R_10K; R_0805_OEM
R4, R5, R11, R12: R_1K; R_0805_OEM
R6, R17: R_120; R_0805_OEM
R7: R_2.2K; R_0805_OEM
R8: R_330; R_0805_OEM
R9: R_1.43K; R_0805_OEM
R10: R_1.91K; R_0805_OEM
R14: R_200; R_0805_OEM
R16: R_0_2512; R_2512_OEM
TP1, TP2, TP3, TP4: TP; tp_1.6mm
U1, U6: MCP25625-x-SS; SSOP-28_5.3x10.2mm_P0.65mm
U2: ATmega328P-AU; TQFP-32_7x7mm_P0.8mm
U3: Fuse_Holder_Blade; Fuse_Block_Holder
U4: ADG417BN; DIP-8_W7.62mm
U5: AP7370; SOT-23-5
U7: MicroFit_VT_6
Y1, Y2, Y3: Crystal_SMD; Crystal_SMD_FA238

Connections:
+5V: C3.1, C4.1, C5.2, C8.2, C10.2, C11.2, C14.1, C15.1, C16.2, J2.2, R3.1, R8.1, R16.1, TP4.1 (TP), U1.1 (VIO), U1.19 (VDD), U1.27 (VDDA), U2.4 (VCC), U2.6 (VCC), U2.18 (AVCC), U6.1 (VIO), U6.19 (VDD), U6.27 (VDDA)
+12V: TP3.1 (TP), U3.1, U7.1
/CAR_CAN_+: R6.1, U1.4 (CANH), U7.3
/CAR_CS: U1.17 (~CS), U2.1 ((PCINT19/OC2B/INT1)PD3)
/CAR_RESET: U1.18 (~RESET), U2.30 ((RXD/PCINT16)PD0)
/CAR_STBY: U1.5 (STBY), U2.9 ((PCINT21/OC0B/T1)PD5)
/CHARGER_CAN_+: R17.1, U6.4 (CANH), U7.5
/CHARGER_CAN_-: R17.2, U6.3 (CANL), U7.6
/CHARGER_CS: U2.32 ((INT0/PCINT18)PD2), U6.17 (~CS)
/CHARGER_RESET: U2.31 ((TXD/PCINT17)PD1), U6.18 (~RESET)
/CHARGER_STBY: U2.2 ((PCINT20/XCK/T0)PD4), U6.5 (STBY)
/EVSE PWM: R10.2, R11.1, U2.23 ((ADC0/PCINT8)PC0)
/MISO: J2.1, R1.1, R13.1, U2.16 ((PCINT3/MISO)PB4)
/MOSI: J2.4, R2.1, R15.1, U2.15 ((PCINT3/OC2A/MOSI)PB3)
/RESET: J2.5, R3.2, U2.29 ((~RESET/PCINT14)PC6)
/SCK: J2.3, U1.14 (SCK), U2.17 ((SCK/PCINT5)PB5), U6.14 (SCK)
/control_pilot: J1.2, Q1.1 (G), Q1.2 (S), TP1.1 (TP)
/proximity_pilot: J1.1, R7.2, R8.2, TP2.1 (TP)
GND: C1.2, C2.2, C3.2, C4.2, C5.1, C6.2, C7.2, C8.1, C9.2, C10.1, C11.1, C12.2, C13.2, C14.2, C15.2, C16.1, C17.2, C18.2, D1.1 (K), D2.1 (K), D3.2 (A), D4.1 (K), D5.1 (K), J2.6, R7.1, R9.2, R11.2, U1.10 (GND), U1.26 (VSS), U2.3 (GND), U2.5 (GND), U2.21 (GND), U5.2 (GND), U6.10 (GND), U6.26 (VSS), U7.2, Y1.2, Y1.4, Y2.2, Y2.4, Y3.2, Y3.4
unnamed: C1.1, U2.8 ((PCINT7/XTAL2/TOSC2)PB7), Y1.1
unnamed: C2.1, U2.7 ((PCINT6/XTAL1/TOSC1)PB6), Y1.3
unnamed: C6.1, U1.9 (OSC1), Y2.1
unnamed: C7.1, U1.8 (OSC2), Y2.3
unnamed: C9.1, U2.20 (AREF)
unnamed: C12.1, D3.1 (K), R12.1, U3.2, U5.1 (Vin)
unnamed: C13.1, F1.1, U5.5 (Vout)
unnamed: C17.1, U6.9 (OSC1), Y3.1
unnamed: C18.1, U6.8 (OSC2), Y3.3
unnamed: D1.2 (A), R4.1
unnamed: D2.2 (A), R5.1
unnamed: D4.2 (A), R12.2
unnamed: D5.2 (A), R14.2
unnamed: F1.2, R14.1, R16.2
unnamed: Q1.3 (D), R10.1, U4.1
unnamed: R1.2, U1.16 (SO)
unnamed: R2.2, U1.15 (SI)
unnamed: R4.2, U2.24 ((ADC1/PCINT9)PC1)
unnamed: R5.2, U2.25 ((ADC2/PCINT10)PC2)
unnamed: R6.2, U1.3 (CANL)
unnamed: R9.1, U4.8
unnamed: R13.2, U6.16 (SO)
unnamed: R15.2, U6.15 (SI)
unnamed: U1.20 (TxCAN), U1.24 (TXD)
unnamed: U1.21 (RxCAN), U1.28 (RXD)
unnamed: U6.20 (TxCAN), U6.24 (TXD)
unnamed: U6.21 (RxCAN), U6.28 (RXD)
